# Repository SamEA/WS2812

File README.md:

WS2812
======
Breakout Board for the WS2812 RGB chip

WS2812 Datasheet: http://www.adafruit.com/datasheets/WS2812.pdf

WS2812.lib : A eagle library for the new WS2812B RGB LED chip

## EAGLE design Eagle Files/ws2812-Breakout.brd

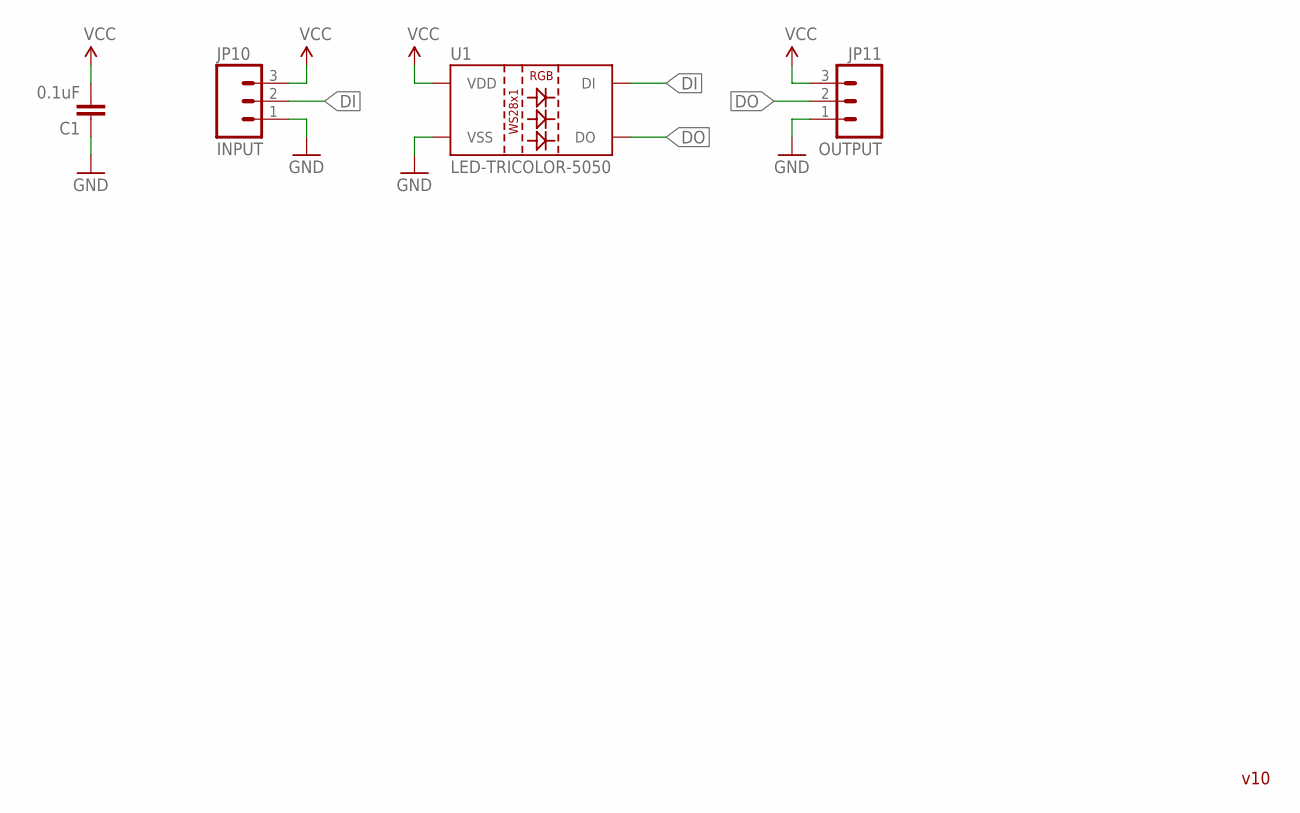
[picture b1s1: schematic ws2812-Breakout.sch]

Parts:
C1: 0.1uF; 0603-CAP
JP10: INPUT; 1X03
JP11: OUTPUT; 1X03
U1: LED-TRICOLOR-5050; LED-TRICOLOR-5050-IC

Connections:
DI: JP10.2, U1.2 (DI)
DO: JP11.2, U1.1 (DO)
GND: C1.1, JP10.1, JP11.1, U1.6 (VSS)
VCC: C1.2, JP10.3, JP11.3, U1.3 (VDD), U1.5 (VDD)

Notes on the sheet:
v10

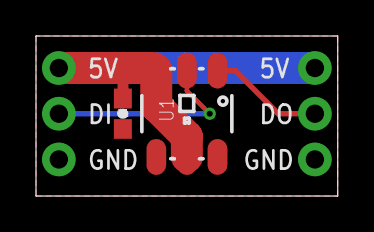
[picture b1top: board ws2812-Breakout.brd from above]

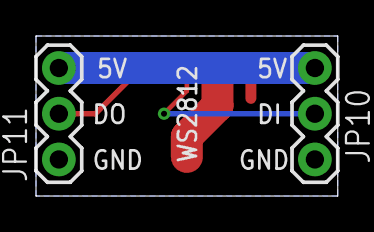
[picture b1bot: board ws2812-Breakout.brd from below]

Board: 2 copper layers, 16.8 x 8.9 mm, 4 parts (2 on the bottom side), 4 nets.

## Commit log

2013-10-14 Added images + Breakout Schematic

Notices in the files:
parts and their libraries:
SparkFun-LED: Licensing: CC v3.0 Share-Alike You are welcome to use this library for commercial purposes.
